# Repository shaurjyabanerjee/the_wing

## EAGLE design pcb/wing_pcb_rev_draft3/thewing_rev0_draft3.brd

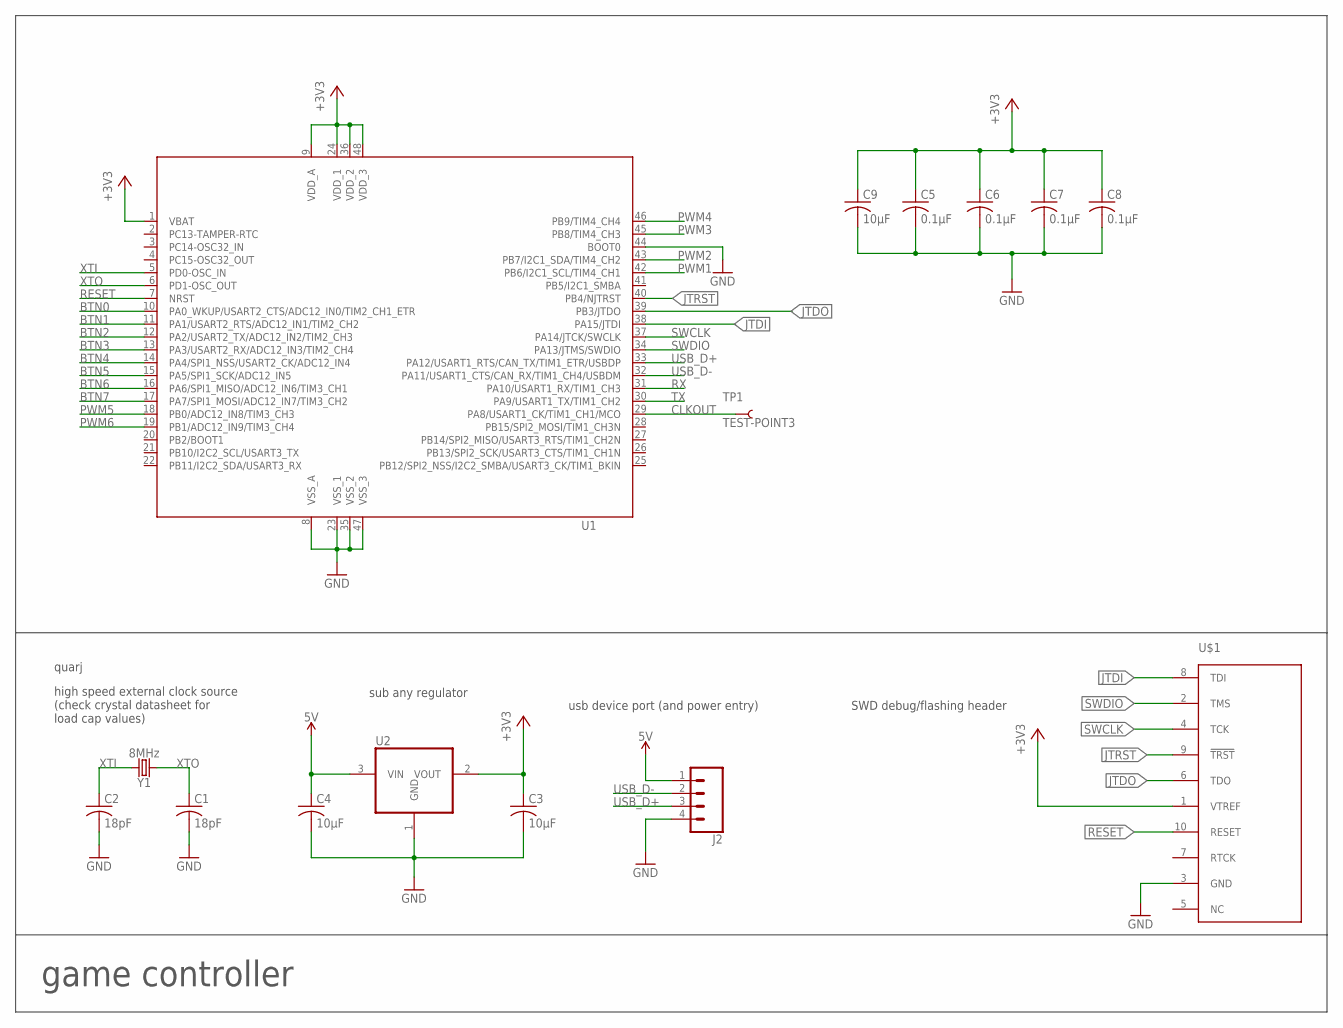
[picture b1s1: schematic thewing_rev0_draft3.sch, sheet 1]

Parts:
C1, C2: 18pF; RCL_C0805K
C3, C4, C9: 10µF; RCL_C0805K
C5, C6, C7, C8: 0.1µF; RCL_C0805K
J2: CONN_04; 1X04
TP1: TEST-POINT3; PAD.03X.03
U1: STM32_STM32F102C4; STM32_LQFP48
U2: OG-VREG_REG1117; OG-VREG_SOT223
U$1: TC2050-NL-MCP-NL; TC2030-MCP-NL
Y1: 8MHz; HC49UP

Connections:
5V: C4.1, J2.1, U2.3 (VIN)
+3V3: C3.1, C5.1, C6.1, C7.1, C8.1, C9.1, U1.1 (VBAT), U1.9 (VDD_A), U1.24 (VDD_1), U1.36 (VDD_2), U1.48 (VDD_3), U2.2 (VOUT), U$1.1 (VTREF); also elsewhere on the board
BTN0: U1.10 (PA0_WKUP/USART2_CTS/ADC12_IN0/TIM2_CH1_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); also elsewhere on the board
BTN1: U1.11 (PA1/USART2_RTS/ADC12_IN1/TIM2_CH2); also elsewhere on the board
BTN2: U1.12 (PA2/USART2_TX/ADC12_IN2/TIM2_CH3); also elsewhere on the board
BTN3: U1.13 (PA3/USART2_RX/ADC12_IN3/TIM2_CH4); also elsewhere on the board
BTN4: U1.14 (PA4/SPI1_NSS/USART2_CK/ADC12_IN4); also elsewhere on the board
BTN5: U1.15 (PA5/SPI1_SCK/ADC12_IN5); also elsewhere on the board
BTN6: U1.16 (PA6/SPI1_MISO/ADC12_IN6/TIM3_CH1); also elsewhere on the board
BTN7: U1.17 (PA7/SPI1_MOSI/ADC12_IN7/TIM3_CH2); also elsewhere on the board
CLKOUT: TP1.P$1, U1.29 (PA8/USART1_CK/TIM1_CH1/MCO)
GND: C1.2, C2.2, C3.2, C4.2, C5.2, C6.2, C7.2, C8.2, C9.2, J2.4, U1.8 (VSS_A), U1.23 (VSS_1), U1.35 (VSS_2), U1.44 (BOOT0), U1.47 (VSS_3), U2.1 (GND), U$1.3 (GND); also elsewhere on the board
JTDI: U1.38 (PA15/JTDI), U$1.8 (TDI)
JTDO: U1.39 (PB3/JTDO), U$1.6 (TDO)
JTRST: U1.40 (PB4/NJTRST), U$1.9 (!TRST)
PWM1: U1.42 (PB6/I2C1_SCL/TIM4_CH1); also elsewhere on the board
PWM2: U1.43 (PB7/I2C1_SDA/TIM4_CH2); also elsewhere on the board
PWM3: U1.45 (PB8/TIM4_CH3); also elsewhere on the board
PWM4: U1.46 (PB9/TIM4_CH4); also elsewhere on the board
PWM5: U1.18 (PB0/ADC12_IN8/TIM3_CH3); also elsewhere on the board
PWM6: U1.19 (PB1/ADC12_IN9/TIM3_CH4); also elsewhere on the board
RESET: U1.7 (NRST), U$1.10 (RESET)
RX: U1.31 (PA10/USART1_RX/TIM1_CH3)
SWCLK: U1.37 (PA14/JTCK/SWCLK), U$1.4 (TCK)
SWDIO: U1.34 (PA13/JTMS/SWDIO), U$1.2 (TMS)
TX: U1.30 (PA9/USART1_TX/TIM1_CH2)
USB_D+: J2.3, U1.33 (PA12/USART1_RTS/CAN_TX/TIM1_ETR/USBDP)
USB_D-: J2.2, U1.32 (PA11/USART1_CTS/CAN_RX/TIM1_CH4/USBDM)
XTI: C2.1, U1.5 (PD0-OSC_IN), Y1.2
XTO: C1.1, U1.6 (PD1-OSC_OUT), Y1.1

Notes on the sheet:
SWD debug/flashing header
high speed external clock source (check crystal datasheet for load cap values)
game controller
sub any regulator
usb device port (and power entry)
quarj

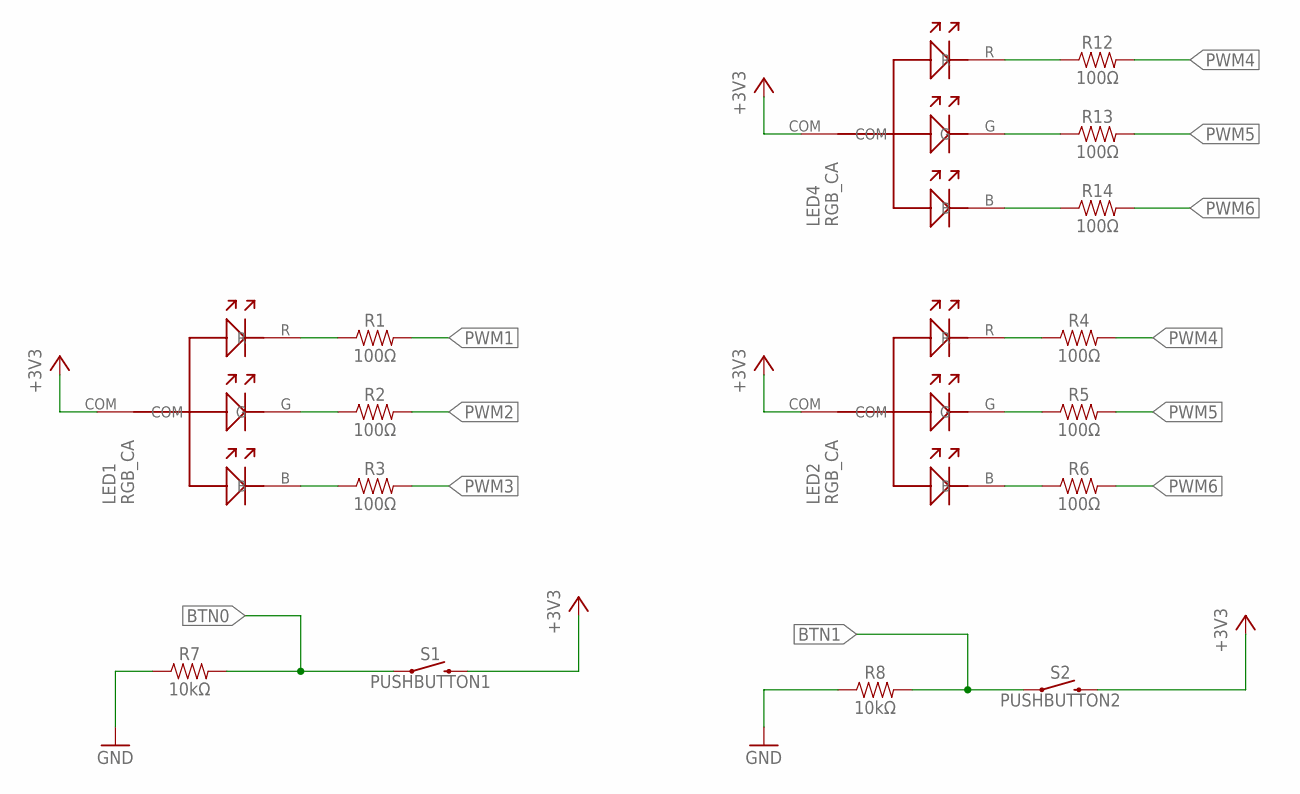
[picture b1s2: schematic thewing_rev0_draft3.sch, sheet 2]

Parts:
LED1, LED2, LED4: RGB_CA; RGB_LED_RECTANGULAR_COMMON_ANODE
R1, R2, R3, R4, R5, R6, R12, R13, R14: 100Ω; 0805
R7, R8: 10kΩ; 0805
S1: PUSHBUTTON1; TACTILE_SWITCH_PTH_6.0MM
S2: PUSHBUTTON2; TACTILE_SWITCH_PTH_6.0MM

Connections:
+3V3: LED1.COM, LED2.COM, LED4.COM, S1.3 (2), S2.3 (2); also elsewhere on the board
BTN0: R7.2, S1.1; also elsewhere on the board
BTN1: R8.2, S2.1; also elsewhere on the board
GND: R7.1, R8.1; also elsewhere on the board
unnamed: LED1.R, R1.1
unnamed: LED1.G, R2.1
unnamed: LED1.B, R3.1
unnamed: LED2.R, R4.1
unnamed: LED2.G, R5.1
unnamed: LED2.B, R6.1
unnamed: LED4.R, R12.1
unnamed: LED4.G, R13.1
unnamed: LED4.B, R14.1
PWM1: R1.2; also elsewhere on the board
PWM2: R2.2; also elsewhere on the board
PWM3: R3.2; also elsewhere on the board
PWM4: R4.2, R12.2; also elsewhere on the board
PWM5: R5.2, R13.2; also elsewhere on the board
PWM6: R6.2, R14.2; also elsewhere on the board

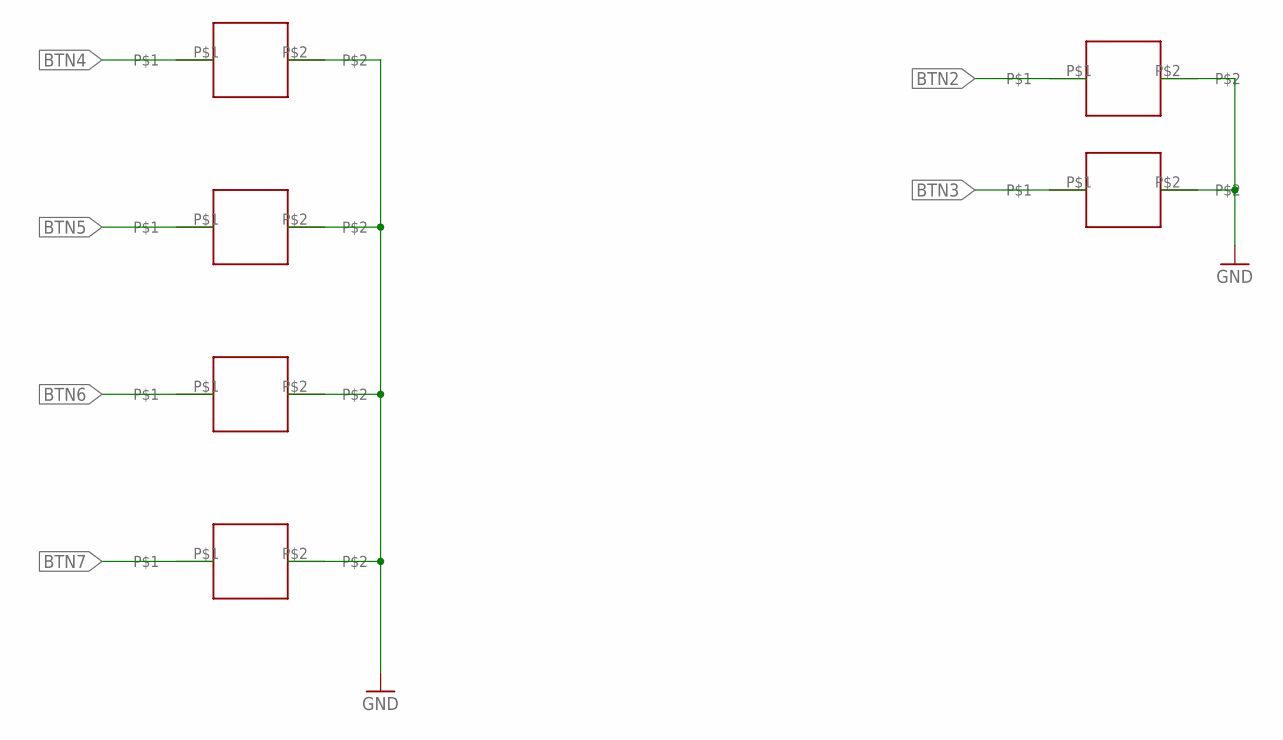
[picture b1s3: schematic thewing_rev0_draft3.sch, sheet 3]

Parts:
A: HYPERKIN_TOUCHPAD_CADET; HYPERKIN_TOUCHPLATE_CADET
B: HYPERKIN_TOUCHPAD_CADET; HYPERKIN_TOUCHPLATE_CADET
D: HYPERKIN_TOUCHPAD_CADET; HYPERKIN_TOUCHPLATE_CADET
L: HYPERKIN_TOUCHPAD_CADET; HYPERKIN_TOUCHPLATE_CADET
R: HYPERKIN_TOUCHPAD_CADET; HYPERKIN_TOUCHPLATE_CADET
U: HYPERKIN_TOUCHPAD_CADET; HYPERKIN_TOUCHPLATE_CADET

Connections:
BTN2: A.P$1; also elsewhere on the board
BTN3: B.P$1; also elsewhere on the board
BTN4: U.P$1; also elsewhere on the board
BTN5: D.P$1; also elsewhere on the board
BTN6: L.P$1; also elsewhere on the board
BTN7: R.P$1; also elsewhere on the board
GND: A.P$2, B.P$2, D.P$2, L.P$2, R.P$2, U.P$2; also elsewhere on the board

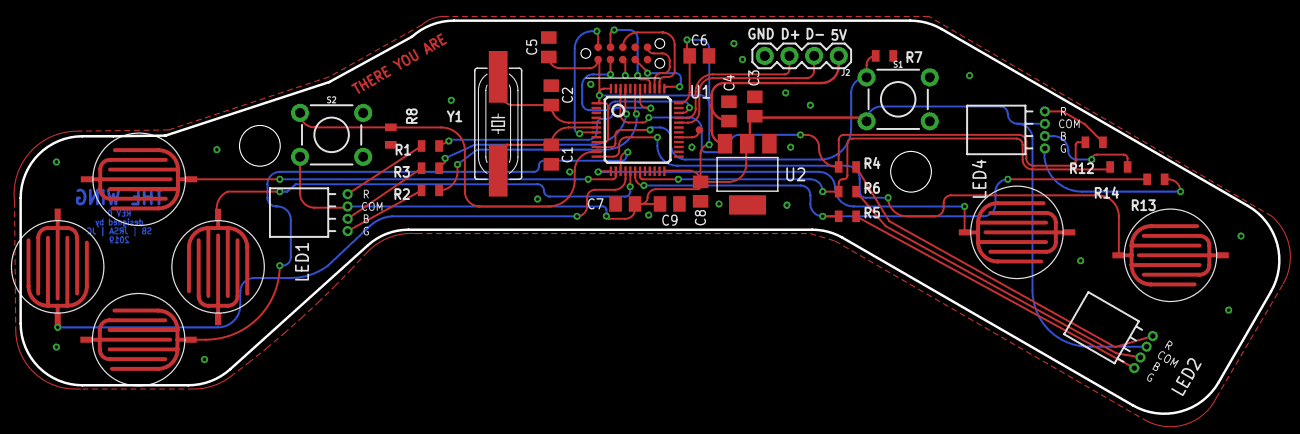
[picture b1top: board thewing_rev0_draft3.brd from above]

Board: 2 copper layers, 129.5 x 40.5 mm, 37 parts (0 on the bottom side), 37 nets.

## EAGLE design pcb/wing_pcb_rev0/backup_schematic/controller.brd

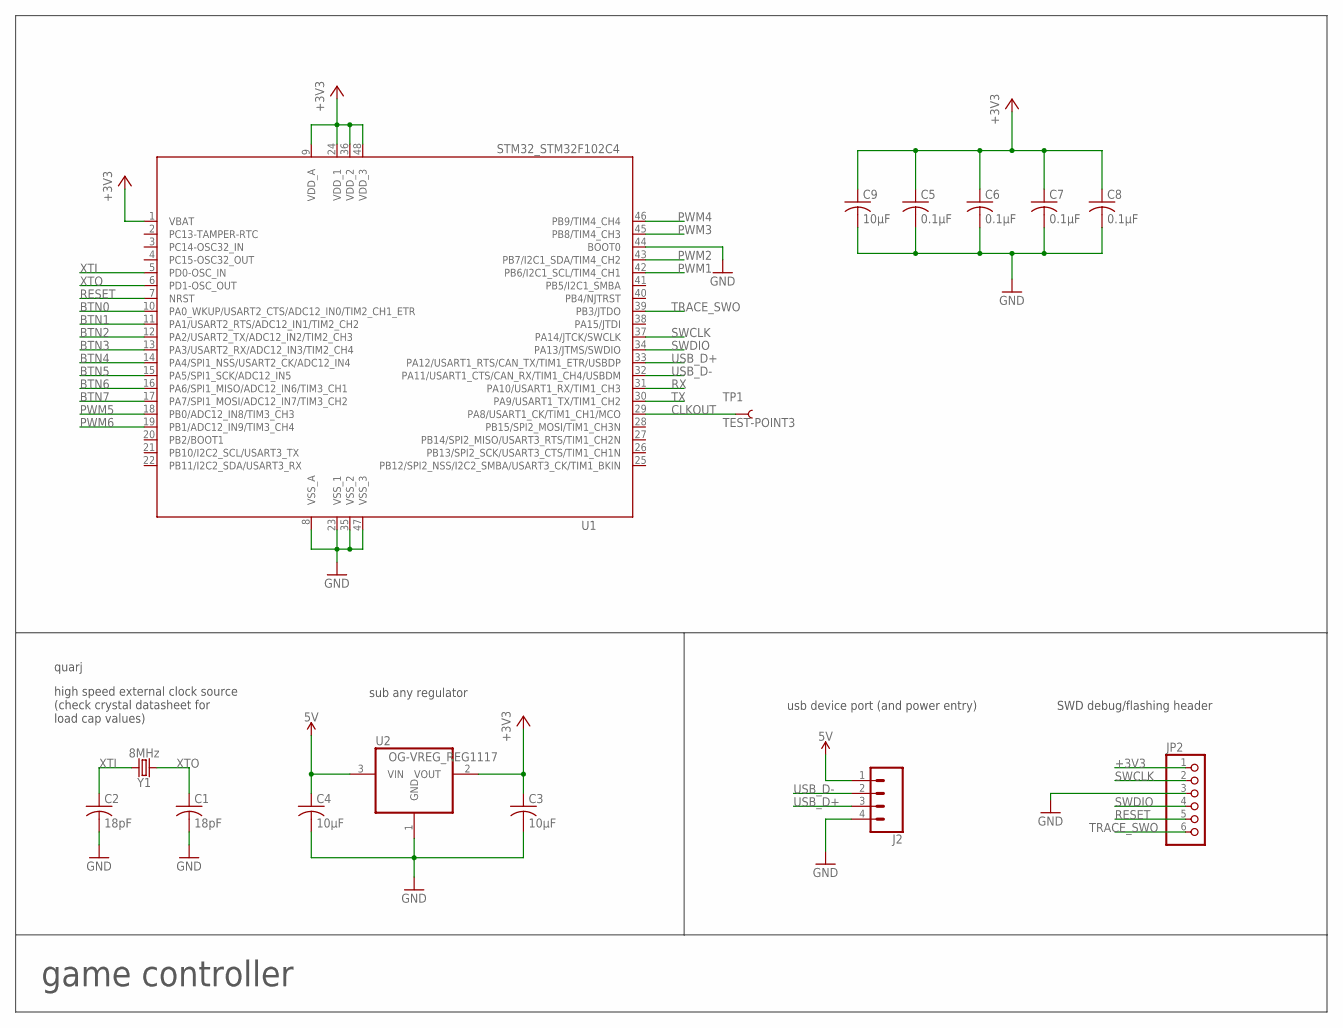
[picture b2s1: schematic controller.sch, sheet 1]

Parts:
C1, C2: 18pF; RCL_C0805K
C3, C4, C9: 10µF; RCL_C0805K
C5, C6, C7, C8: 0.1µF; RCL_C0805K
J2: CONN_04; 1X04
JP2: PINHD-1X6; 1X06
TP1: TEST-POINT3; PAD.03X.03
U1: STM32_STM32F102C4; STM32_LQFP48
U2: OG-VREG_REG1117; OG-VREG_SOT223
Y1: 8MHz; HC49UP

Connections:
5V: C4.1, J2.1, U2.3 (VIN)
+3V3: C3.1, C5.1, C6.1, C7.1, C8.1, C9.1, JP2.1, U1.1 (VBAT), U1.9 (VDD_A), U1.24 (VDD_1), U1.36 (VDD_2), U1.48 (VDD_3), U2.2 (VOUT); also elsewhere on the board
BTN0: U1.10 (PA0_WKUP/USART2_CTS/ADC12_IN0/TIM2_CH1_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)
BTN1: U1.11 (PA1/USART2_RTS/ADC12_IN1/TIM2_CH2); also elsewhere on the board
BTN2: U1.12 (PA2/USART2_TX/ADC12_IN2/TIM2_CH3); also elsewhere on the board
BTN3: U1.13 (PA3/USART2_RX/ADC12_IN3/TIM2_CH4)
BTN4: U1.14 (PA4/SPI1_NSS/USART2_CK/ADC12_IN4)
BTN5: U1.15 (PA5/SPI1_SCK/ADC12_IN5)
BTN6: U1.16 (PA6/SPI1_MISO/ADC12_IN6/TIM3_CH1)
BTN7: U1.17 (PA7/SPI1_MOSI/ADC12_IN7/TIM3_CH2)
CLKOUT: TP1.P$1, U1.29 (PA8/USART1_CK/TIM1_CH1/MCO)
GND: C1.2, C2.2, C3.2, C4.2, C5.2, C6.2, C7.2, C8.2, C9.2, J2.4, JP2.3, U1.8 (VSS_A), U1.23 (VSS_1), U1.35 (VSS_2), U1.44 (BOOT0), U1.47 (VSS_3), U2.1 (GND); also elsewhere on the board
PWM1: U1.42 (PB6/I2C1_SCL/TIM4_CH1); also elsewhere on the board
PWM2: U1.43 (PB7/I2C1_SDA/TIM4_CH2); also elsewhere on the board
PWM3: U1.45 (PB8/TIM4_CH3); also elsewhere on the board
PWM4: U1.46 (PB9/TIM4_CH4); also elsewhere on the board
PWM5: U1.18 (PB0/ADC12_IN8/TIM3_CH3); also elsewhere on the board
PWM6: U1.19 (PB1/ADC12_IN9/TIM3_CH4); also elsewhere on the board
RESET: JP2.5, U1.7 (NRST)
RX: U1.31 (PA10/USART1_RX/TIM1_CH3)
SWCLK: JP2.2, U1.37 (PA14/JTCK/SWCLK)
SWDIO: JP2.4, U1.34 (PA13/JTMS/SWDIO)
TRACE_SWO: JP2.6, U1.39 (PB3/JTDO)
TX: U1.30 (PA9/USART1_TX/TIM1_CH2)
USB_D+: J2.3, U1.33 (PA12/USART1_RTS/CAN_TX/TIM1_ETR/USBDP)
USB_D-: J2.2, U1.32 (PA11/USART1_CTS/CAN_RX/TIM1_CH4/USBDM)
XTI: C2.1, U1.5 (PD0-OSC_IN), Y1.2
XTO: C1.1, U1.6 (PD1-OSC_OUT), Y1.1

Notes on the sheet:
SWD debug/flashing header
high speed external clock source (check crystal datasheet for load cap values)
game controller
sub any regulator
usb device port (and power entry)
quarj

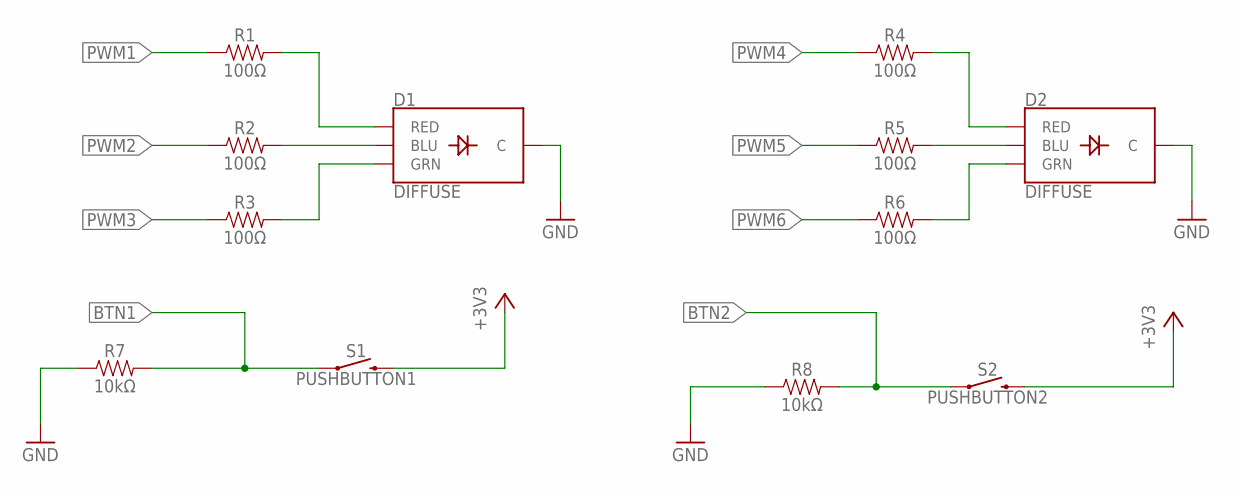
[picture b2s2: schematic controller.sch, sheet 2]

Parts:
D1, D2: DIFFUSE; LED-RGB-THRU
R1, R2, R3, R4, R5, R6: 100Ω; 0805
R7, R8: 10kΩ; 0805
S1: PUSHBUTTON1; TACTILE_SWITCH_PTH_6.0MM
S2: PUSHBUTTON2; TACTILE_SWITCH_PTH_6.0MM

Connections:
+3V3: S1.3 (2), S2.3 (2); also elsewhere on the board
BTN1: R7.2, S1.1; also elsewhere on the board
BTN2: R8.2, S2.1; also elsewhere on the board
GND: D1.2 (C), D2.2 (C), R7.1, R8.1; also elsewhere on the board
unnamed: D1.1 (RED), R1.2
unnamed: D1.4 (BLU), R2.2
unnamed: D1.3 (GRN), R3.2
unnamed: D2.4 (BLU), R5.2
unnamed: D2.1 (RED), R4.2
unnamed: D2.3 (GRN), R6.2
PWM1: R1.1; also elsewhere on the board
PWM2: R2.1; also elsewhere on the board
PWM3: R3.1; also elsewhere on the board
PWM4: R4.1; also elsewhere on the board
PWM5: R5.1; also elsewhere on the board
PWM6: R6.1; also elsewhere on the board

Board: 2 copper layers, 27 parts (0 on the bottom side), 26 nets, no tracks yet.

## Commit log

2019-03-12 designed pcb panel file in eagle

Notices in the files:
parts and their libraries:
SparkFun-Connectors: Licensing: Creative Commons ShareAlike 4.0 International - https://creativecommons.org/licenses/by-sa/4.0
TC2050: ©2009 ROFA.cz
